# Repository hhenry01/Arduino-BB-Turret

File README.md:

# Arduino-BB-Turret
## About
The BB Turret is a project developed for [Zen Maker Lab](https://www.zenmakerlab.com/).

The code found under [BB_Turret](https://github.com/hhenry01/Arduino-BB-Turret/blob/main/BB_Turret/BB_Turret.ino) controls the shooting and aiming functions of the turret.

## How it Works
Full details surrounding the project belong to Zen Maker Lab. This README only describes the code and the circuit.
### Shooting

When a button is pressed, the Arduino outputs two voltages to the L298N module in order to spin a motor. One of the input pins is set to *HIGH* while the other is set to *LOW*. For more information, see an [L298N schematic](https://www.handsontec.com/dataspecs/L298N%20Motor%20Driver.pdf).\
\
The motor spins a gear in a rack and pinion system. The gear pushes the rack against a spring. The gear does not have teeth around its entire circumference, so the rack is eventually released and is propelled forward by a spring, hitting and shooting a projectile.

### Aiming

To aim the turret, a joystick controls the two servo motors. Since servos need specific angles, inputs must be processed. Smooth motion is created by taking the input and resizing it within an acceptable range for speed. Within that range lies different degrees of speed, simulating analog output, which is more intuitive and allows for finer control.\
\
The button in a joystick is not used because a dedicated button is preferable to control the DC motor. Using the joystick button makes it difficult to keep steady and hard to press when holding a direction. With a dedicated button, one can comfortably shoot the turret no matter the situation.\
\
Finally, at the end of the loop, a 10 ms delay is necessary. Without it, any input via the analog stick would cause immediately rotate the servos to their limits.

#### Full Circuit Schematic and Board
\
\
\
The PCB has a ground plane that connects all ground pins to each other.

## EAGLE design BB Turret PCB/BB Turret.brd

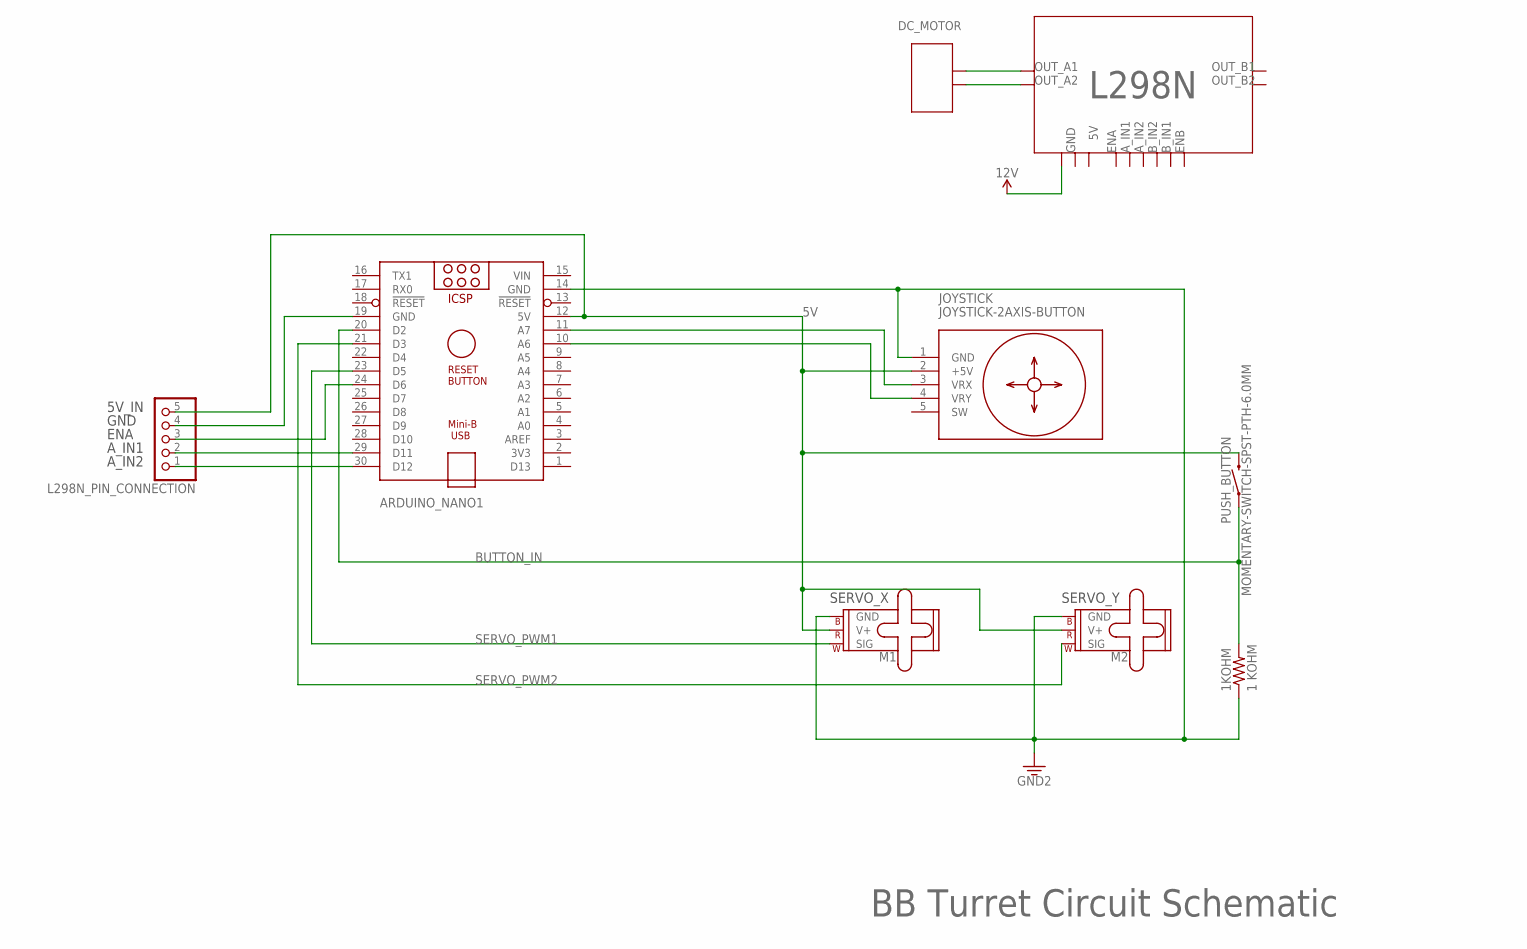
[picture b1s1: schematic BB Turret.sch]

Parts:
1KOHM: 1 KOHM; 0204/7
ARDUINO_NANO1: ARDUINO_NANO
JOYSTICK: JOYSTICK-2AXIS-BUTTON
L298N_PIN_CONNECTION: PINHD-1X5; 1X05
M1, M2: SERVO; 1X03
PUSH_BUTTON: MOMENTARY-SWITCH-SPST-PTH-6.0MM; TACTILE_SWITCH_PTH_6.0MM

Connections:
5V: ARDUINO_NANO1.12 (5V), JOYSTICK.2 (+5V), L298N_PIN_CONNECTION.5, M1.2 (V+), M2.2 (V+), PUSH_BUTTON.3 (2)
A_IN1: ARDUINO_NANO1.29 (D11), L298N_PIN_CONNECTION.2
A_IN2: ARDUINO_NANO1.30 (D12), L298N_PIN_CONNECTION.1
BUTTON_IN: 1KOHM.2, ARDUINO_NANO1.20 (D2), PUSH_BUTTON.1
ENA: ARDUINO_NANO1.24 (D6), L298N_PIN_CONNECTION.3
GND: 1KOHM.1, ARDUINO_NANO1.14 (GND), ARDUINO_NANO1.19 (GND), JOYSTICK.1 (GND), L298N_PIN_CONNECTION.4, M1.3 (GND), M2.3 (GND)
SERVO_PWM1: ARDUINO_NANO1.23 (D5), M1.1 (SIG)
SERVO_PWM2: ARDUINO_NANO1.21 (D3), M2.1 (SIG)
VIN: ARDUINO_NANO1.15 (VIN)
VRX: ARDUINO_NANO1.11 (A7), JOYSTICK.3 (VRX)
VRY: ARDUINO_NANO1.10 (A6), JOYSTICK.4 (VRY)

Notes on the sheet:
BB Turret Circuit Schematic
L298N
GND
OUT_A1
OUT_A2
ENA
A_IN1
A_IN2
B_IN2
B_IN1
ENB
OUT_B1
OUT_B2
DC_MOTOR
5V_IN
SERVO_X
SERVO_Y

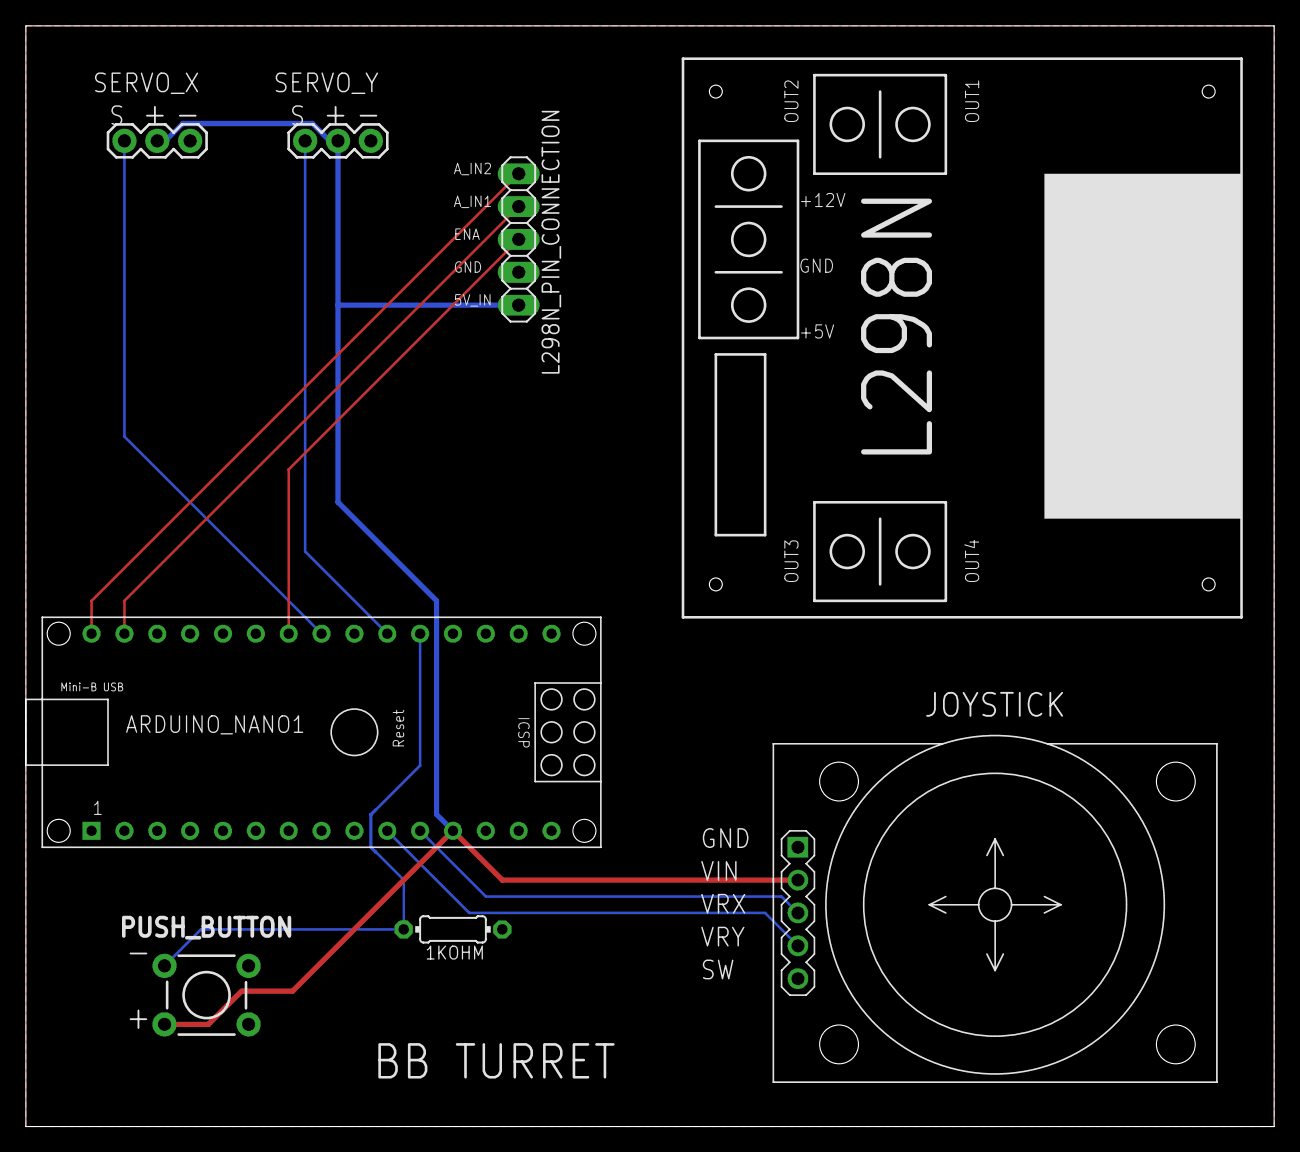
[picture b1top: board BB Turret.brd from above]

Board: 2 copper layers, 96.5 x 85.1 mm, 7 parts (0 on the bottom side), 10 nets.

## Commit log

2021-06-03 Added simple motor control on button press.
2021-06-19 Added aiming code
2021-06-19 Fixed folder structure
2021-06-24 Updated Aiming.ino to have delay.
    Fixes maxing out at the slightest input.
2021-06-24 Added combined control file.
2021-06-25 Added Circuit Diagrams.
2021-06-25 Added README.md
2021-06-26 Added full schematic, updated README.
2021-07-29 Modified code to take advantage of L298N H-bridge
2021-07-29 Removed unnecessary files and modified rotation limits.
2021-08-16 Updated README and images to reflect addition of L298N.
2021-08-16 Switched schematic image for one with a higher resolution.
2021-08-17 Modified BB_Turret.ino so that it uses the correct PWM pins on the Arduino. Need to update images and PCB.
2021-08-17 Minor change to code. Added TODO.txt for current issues and potential fixes.
2021-08-18 Changes listed in TODO.txt didn't work out. May need changes that are too complex. Current iteration is functional.
2021-08-19 Updated PCB files to be up to date with the code and current breadboard circuit. Updated images and README.
2021-08-19 Added missing line regarding ground plane in README.
2021-08-24 Fixed circuit and PCB so that the Arduino does not need USB power.

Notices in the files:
parts and their libraries:
SparkFun-Switches: Licensing: Creative Commons ShareAlike 4.0 International - https://creativecommons.org/licenses/by-sa/4.0
diy-modules: Released under the Creative Commons Attribution 4.0 International License: http://creativecommons.org/licenses/by/4.0
